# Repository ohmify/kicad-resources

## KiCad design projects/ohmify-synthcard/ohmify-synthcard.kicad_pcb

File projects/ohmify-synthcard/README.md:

# SynthCard for Ohmify
A synthesizer business card PCB based on the [Atari Punk Console](https://sdiy.info/wiki/Atari_Punk_Console).

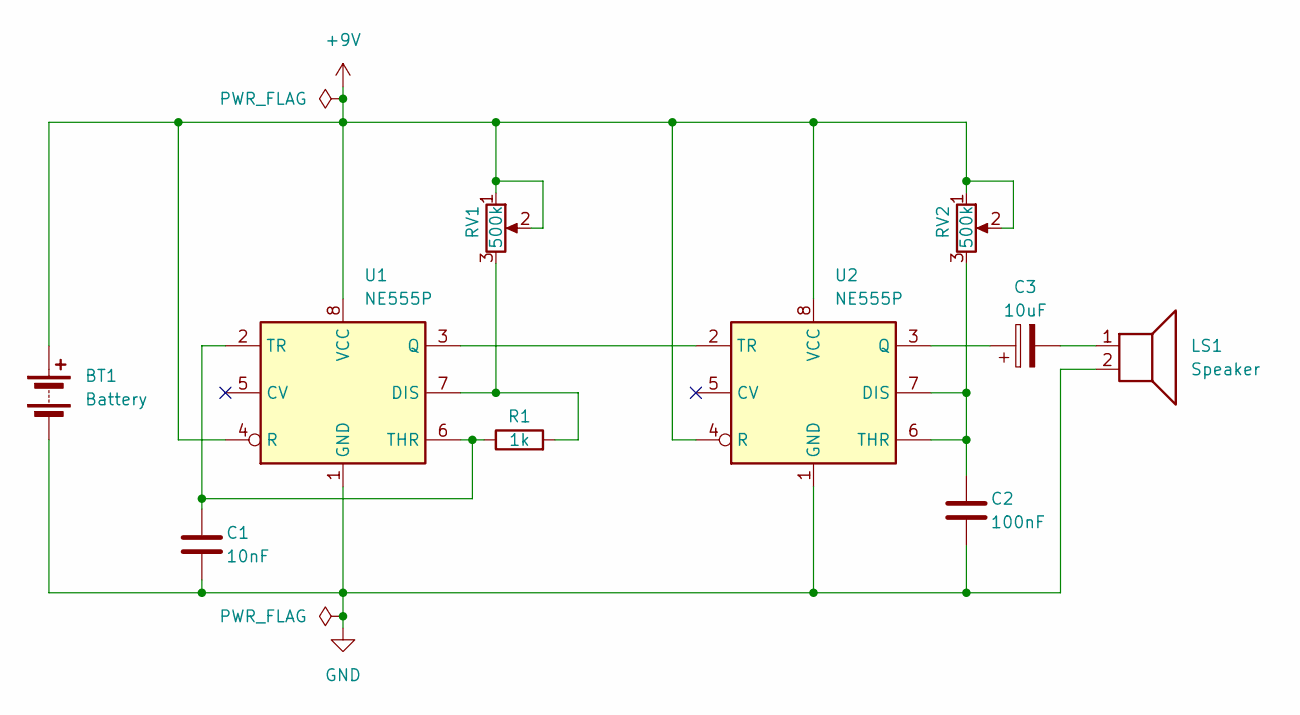
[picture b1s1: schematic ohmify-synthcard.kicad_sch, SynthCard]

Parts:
BT1: Battery; SolderWire-0.5sqmm_1x02_P4.6mm_D0.9mm_OD2.1mm_Relief
C1: 10nF; C_Rect_L7.0mm_W2.5mm_P5.00mm
C2: 100nF; C_Rect_L7.0mm_W2.5mm_P5.00mm
C3: 10uF; CP_Radial_D5.0mm_P2.50mm
LS1: Speaker; SolderWire-0.5sqmm_1x02_P4.6mm_D0.9mm_OD2.1mm
R1: 1k; R_Axial_DIN0207_L6.3mm_D2.5mm_P7.62mm_Horizontal
RV1, RV2: 500k; Potentiometer_Alpha_RD901F-40-00D_Single_Vertical
U1, U2: NE555P; DIP-8_W7.62mm

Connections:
+9V: BT1.1 (+), RV1.1, RV1.2, RV2.1, RV2.2, U1.4 (R), U1.8 (VCC), U2.4 (R), U2.8 (VCC)
GND: BT1.2 (-), C1.2, C2.2, LS1.2, U1.1 (GND), U2.1 (GND)
unnamed: C3.2, LS1.1
unnamed: R1.2, RV1.3, U1.7 (DIS)
unnamed: U1.3 (Q), U2.2 (TR)
unnamed: C1.1, R1.1, U1.2 (TR), U1.6 (THR)
unnamed: C2.1, RV2.3, U2.6 (THR), U2.7 (DIS)
unnamed: C3.1, U2.3 (Q)

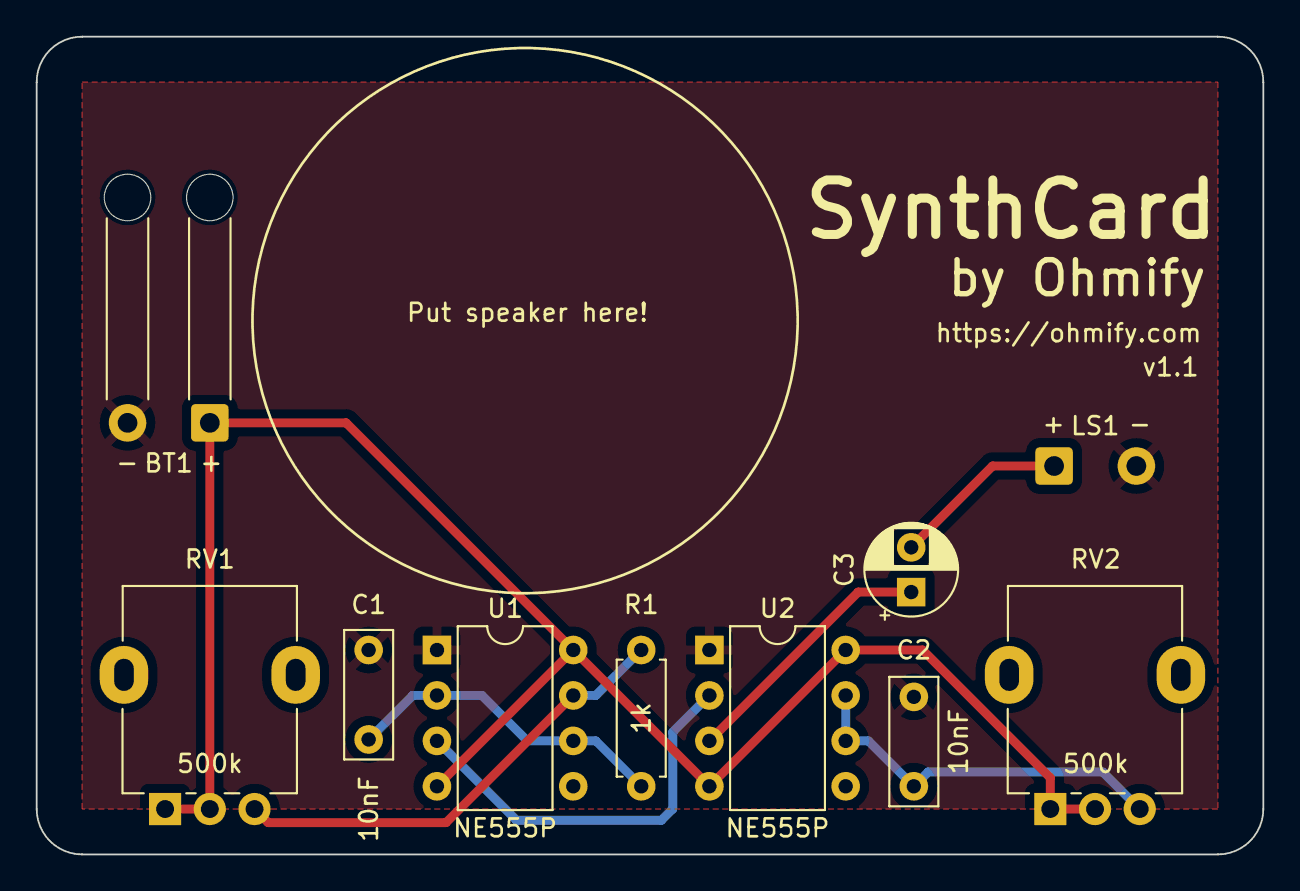
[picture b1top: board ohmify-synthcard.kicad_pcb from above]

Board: 2 copper layers, 68.6 x 45.7 mm, 10 parts (0 on the bottom side), 8 nets.

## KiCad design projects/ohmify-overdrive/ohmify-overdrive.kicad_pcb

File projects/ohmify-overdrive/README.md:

# Ohmify Overdrive

A simple overdrive pedal PCB.

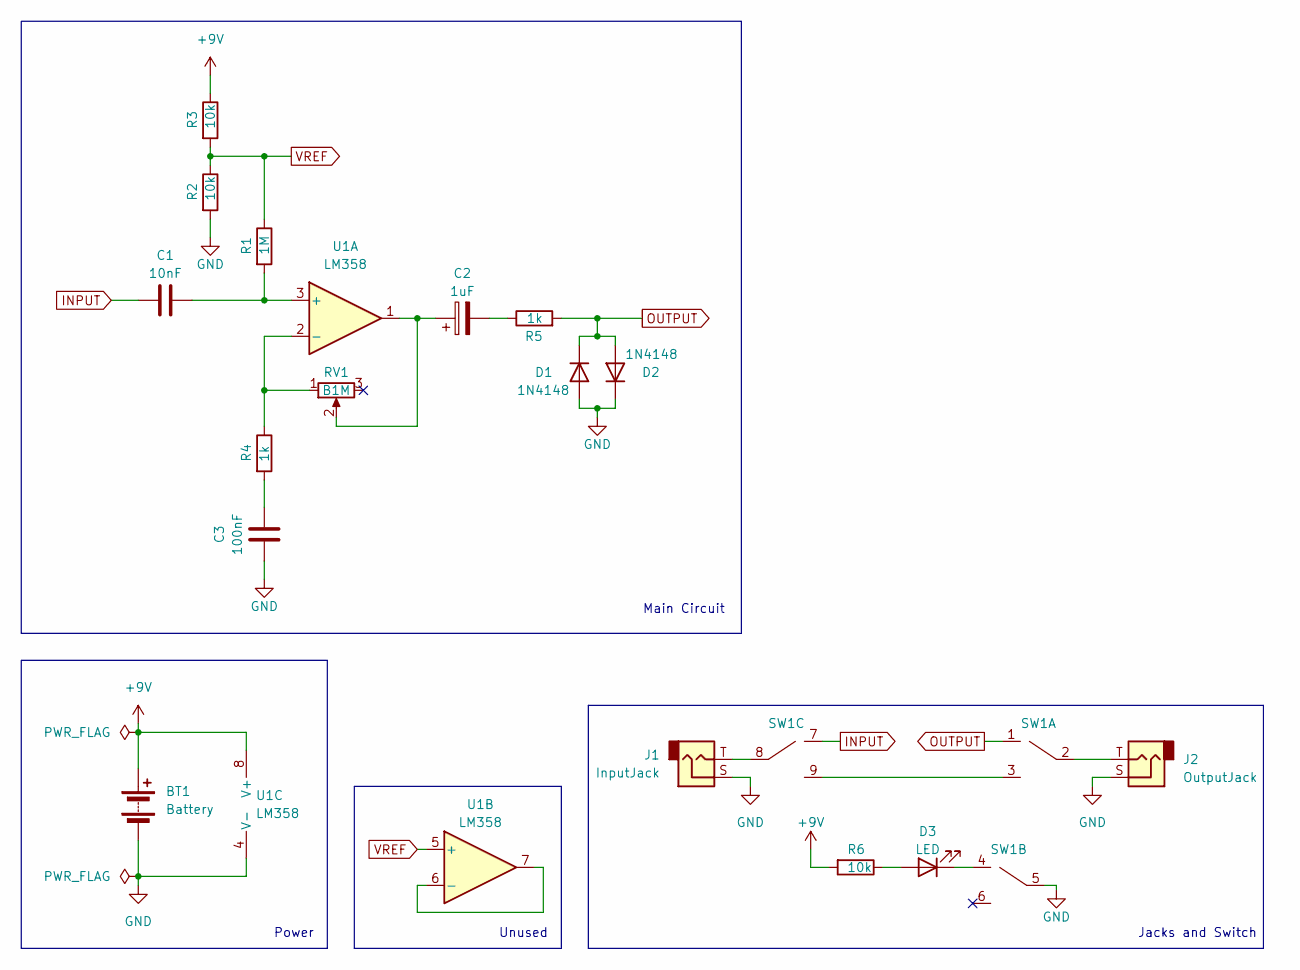
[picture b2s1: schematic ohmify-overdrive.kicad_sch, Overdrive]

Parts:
BT1: Battery; SolderWire-0.5sqmm_1x02_P4.6mm_D0.9mm_OD2.1mm
C1: 10nF; C_Rect_L7.0mm_W3.5mm_P5.00mm
C2: 1uF; C_Radial_D6.3mm_H5.0mm_P2.50mm
C3: 100nF; C_Rect_L7.0mm_W3.5mm_P5.00mm
D1, D2: 1N4148; D_DO-35_SOD27_P7.62mm_Horizontal
D3: LED; LED_D5.0mm
J1: InputJack; SolderWire-0.5sqmm_1x02_P4.6mm_D0.9mm_OD2.1mm
J2: OutputJack; SolderWire-0.5sqmm_1x02_P4.6mm_D0.9mm_OD2.1mm
R1: 1M; R_Axial_DIN0207_L6.3mm_D2.5mm_P7.62mm_Horizontal
R2, R3, R6: 10k; R_Axial_DIN0207_L6.3mm_D2.5mm_P7.62mm_Horizontal
R4, R5: 1k; R_Axial_DIN0207_L6.3mm_D2.5mm_P7.62mm_Horizontal
RV1: B1M; SolderWire-0.5sqmm_1x03_P4.6mm_D0.9mm_OD2.1mm
SW1: Switch_3PDT
U1: LM358; DIP-8_W7.62mm

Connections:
+9V: BT1.1 (+), R3.1, R6.2, U1.8 (V+)
GND: BT1.2 (-), C3.1, D1.2 (A), D2.1 (K), J1.S, J2.S, R2.2, SW1.5, U1.4 (V-)
INPUT: C1.1, SW1.7
unnamed: C2.1, RV1.2, U1.1
unnamed: C2.2, R5.1
unnamed: C3.2, R4.2
unnamed: D3.2 (A), R6.1
unnamed: D3.1 (K), SW1.4
unnamed: J1.T, SW1.8
unnamed: J2.T, SW1.2
unnamed: SW1.3, SW1.9
unnamed: C1.2, R1.2, U1.3 (+)
unnamed: R4.1, RV1.1, U1.2 (-)
unnamed: U1.6 (-), U1.7
OUTPUT: D1.1 (K), D2.2 (A), R5.2, SW1.1
VREF: R1.1, R2.1, R3.2, U1.5 (+)

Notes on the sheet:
Unused
Power
Jacks and Switch
Main Circuit

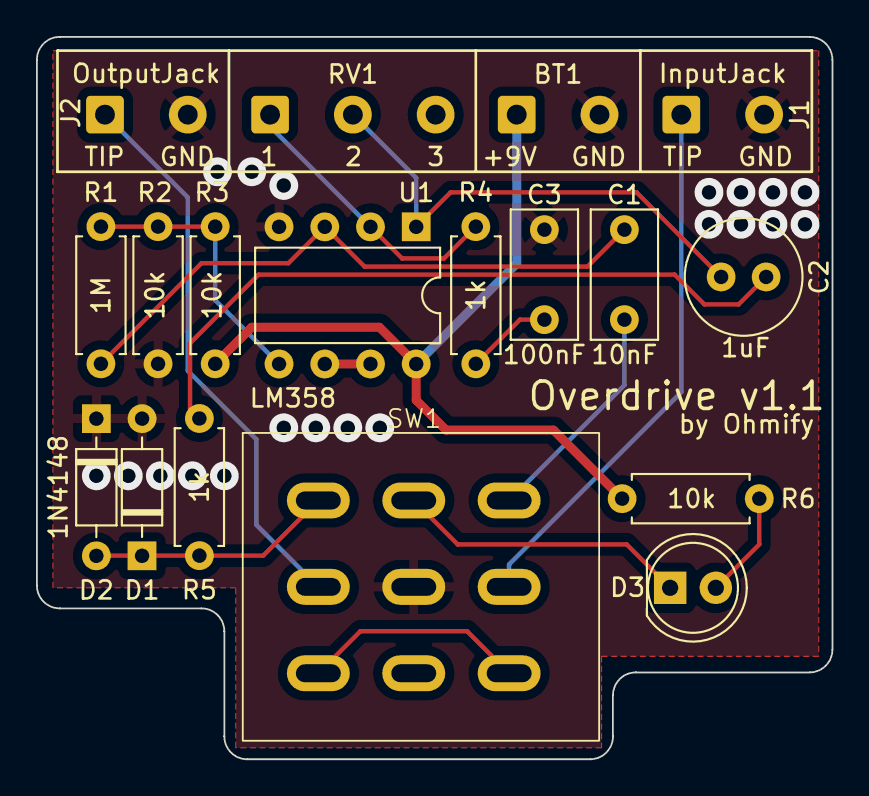
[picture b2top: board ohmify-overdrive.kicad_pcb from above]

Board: 2 copper layers, 44.2 x 40.1 mm, 18 parts (0 on the bottom side), 16 nets.

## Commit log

2023-11-29 Added 3PDT footprint and symbol
2023-11-29 Added overdrive and synthcard KiCAD projects
2023-11-29 Added project for synthcard
2023-11-29 Added description for symbols
2024-02-09 Fixed 3DPT symbol for the overdrive
2024-02-10 Fixed synthcard, added new gerber files
2024-04-04 Working v1.1 synthcard
2024-04-04 Added link to APC
